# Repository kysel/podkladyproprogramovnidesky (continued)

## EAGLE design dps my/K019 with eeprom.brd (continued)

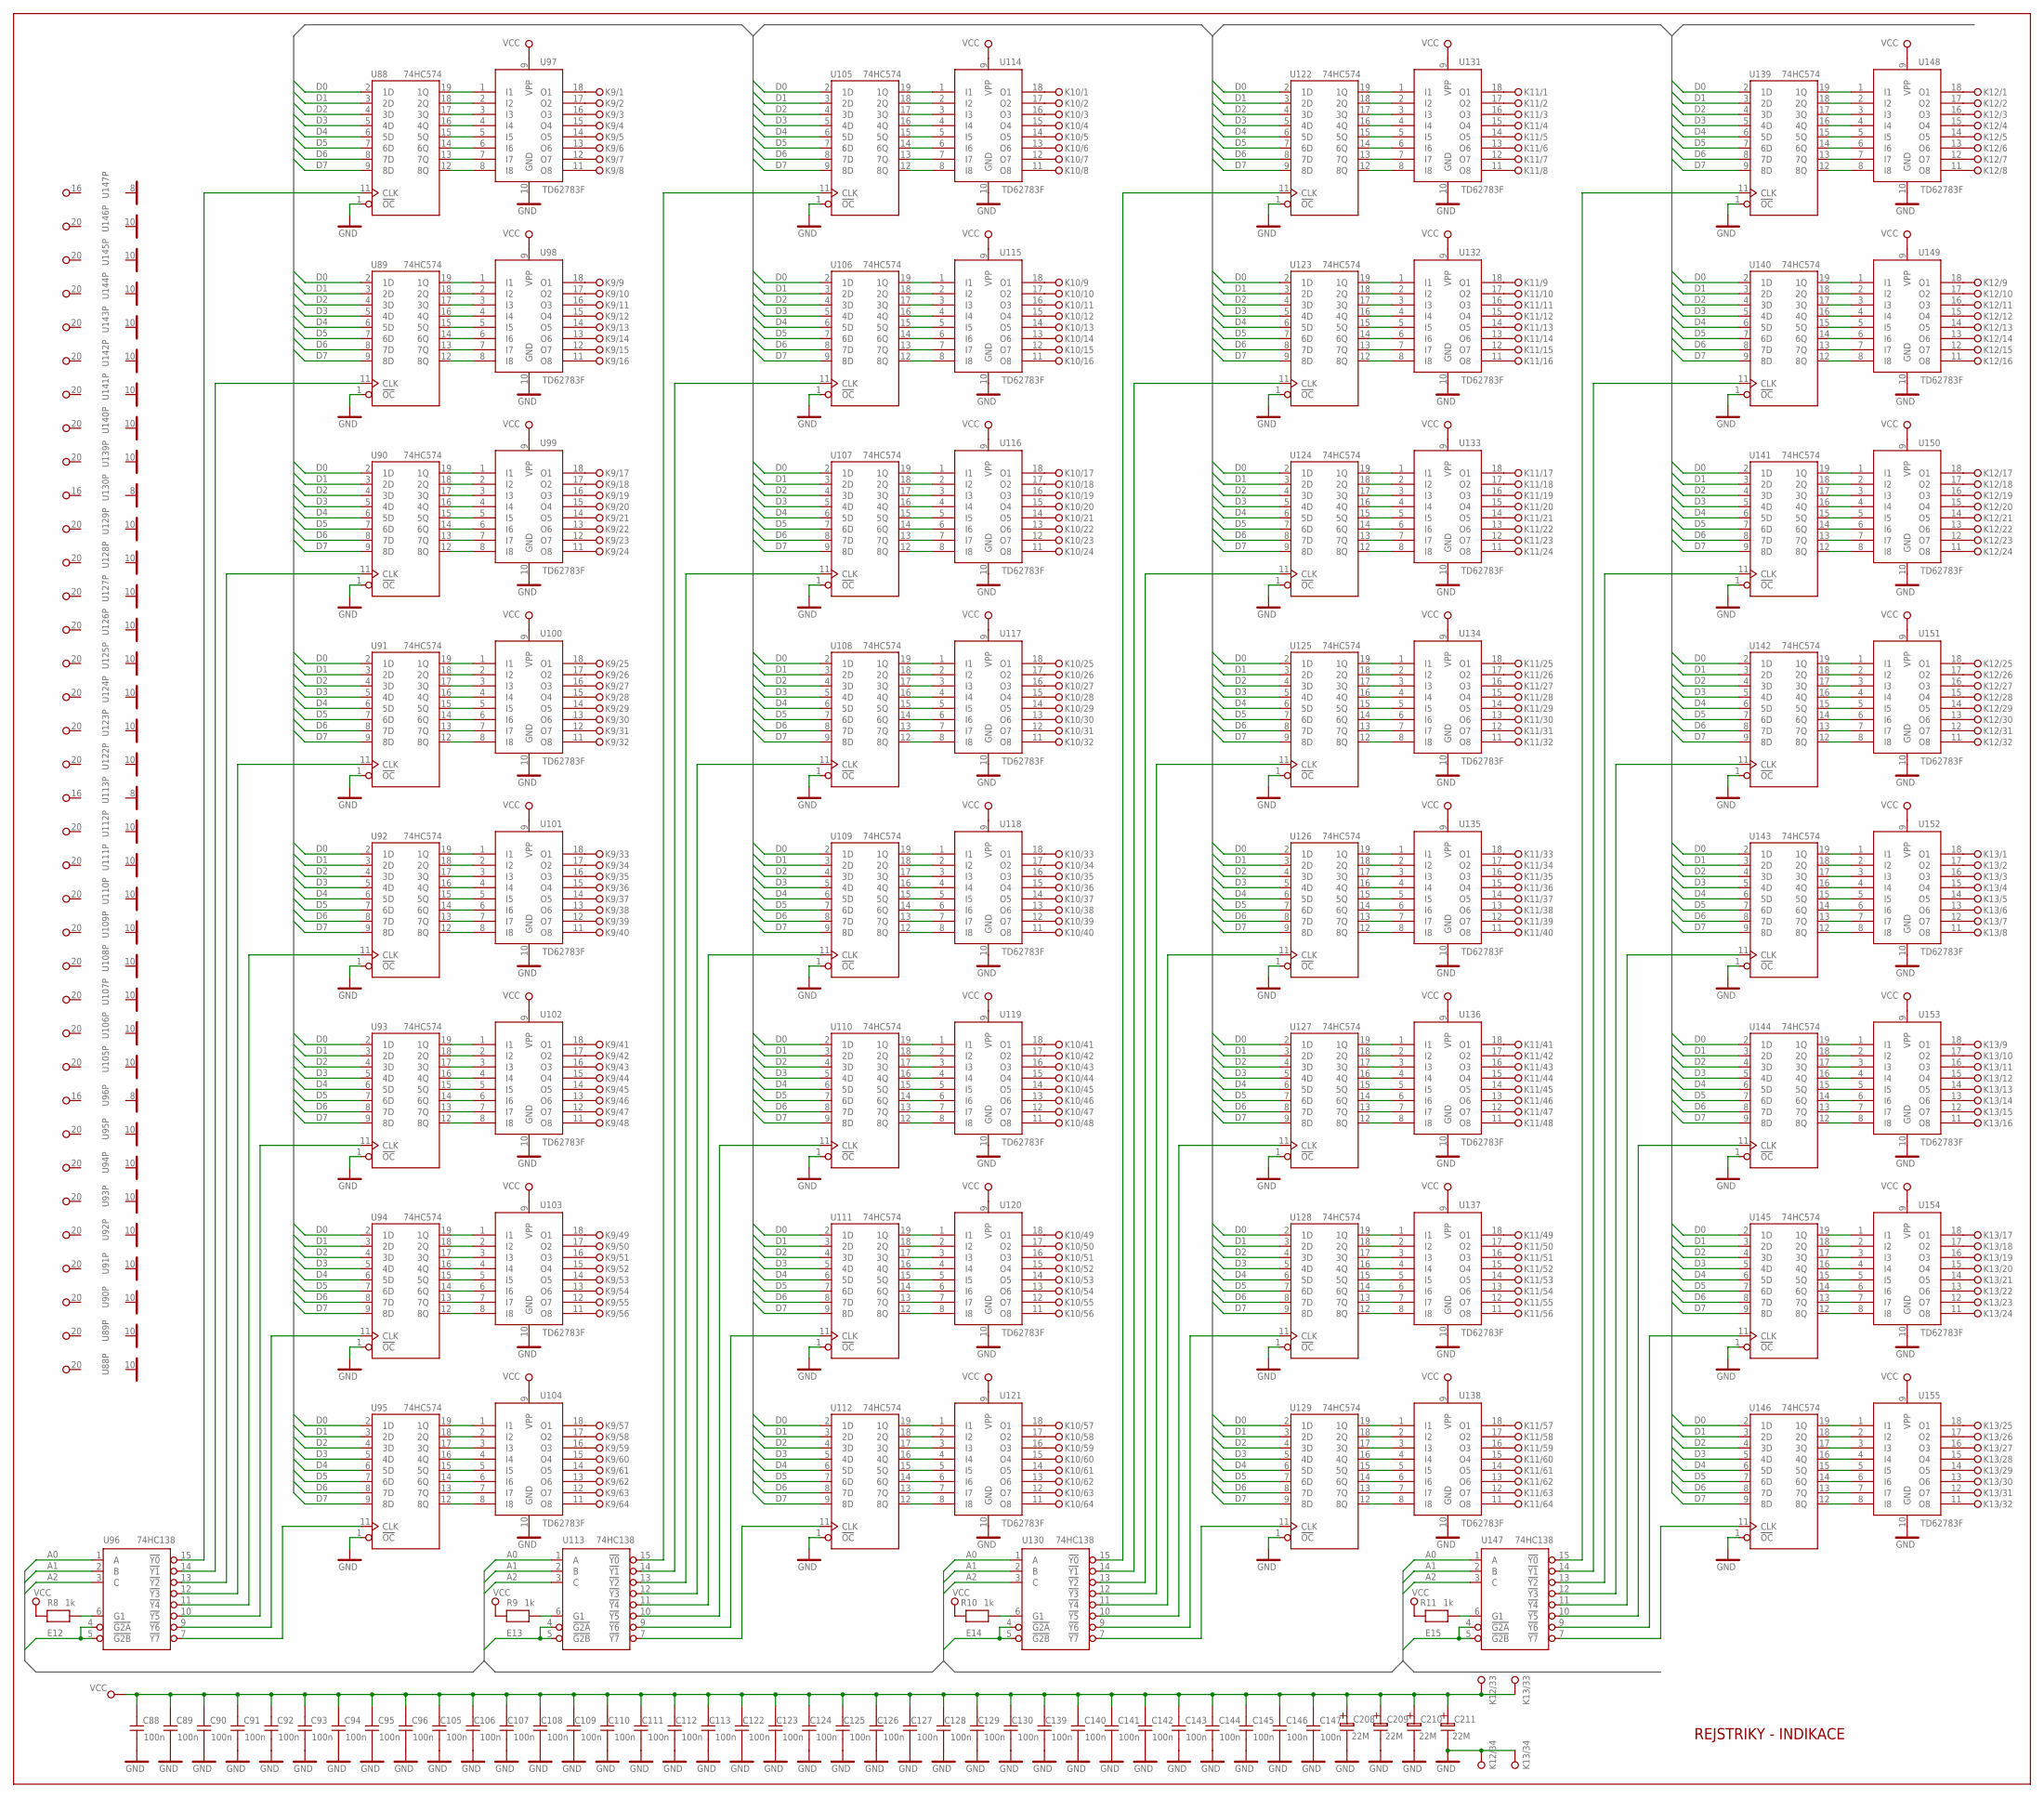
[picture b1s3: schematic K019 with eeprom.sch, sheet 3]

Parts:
C88, C89, C90, C91, C92, C93, C94, C95, C96, C105, C106, C107, C108, C109, C110, C111, C112, C113, C122, C123, C124, C125, C126, C127, C128, C129, C130, C139, C140, C141, C142, C143, C144, C145, C146, C147: 100n; C-5-2X8
C208, C209, C210, C211: 22M; EC-2/5
K9, K10, K11: KON64
K12, K13: KON34
R8, R9, R10, R11: 1k; R-7,5
U88, U89, U90, U91, U92, U93, U94, U95, U105, U106, U107, U108, U109, U110, U111, U112, U122, U123, U124, U125, U126, U127, U128, U129, U139, U140, U141, U142, U143, U144, U145, U146: 74HC574; DIL20
U96, U113, U130, U147: 74HC138; DIL16
U97, U98, U99, U100, U101, U102, U103, U104, U114, U115, U116, U117, U118, U119, U120, U121, U131, U132, U133, U134, U135, U136, U137, U138, U148, U149, U150, U151, U152, U153, U154, U155: TD62783F; DIL18

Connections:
A0: U96.1 (A), U113.1 (A), U130.1 (A), U147.1 (A); also elsewhere on the board
A1: U96.2 (B), U113.2 (B), U130.2 (B), U147.2 (B); also elsewhere on the board
A2: U96.3 (C), U113.3 (C), U130.3 (C), U147.3 (C); also elsewhere on the board
D0: U88.2 (1D), U89.2 (1D), U90.2 (1D), U91.2 (1D), U92.2 (1D), U93.2 (1D), U94.2 (1D), U95.2 (1D), U105.2 (1D), U106.2 (1D), U107.2 (1D), U108.2 (1D), U109.2 (1D), U110.2 (1D), U111.2 (1D), U112.2 (1D), U122.2 (1D), U123.2 (1D), U124.2 (1D), U125.2 (1D), U126.2 (1D), U127.2 (1D), U128.2 (1D), U129.2 (1D), U139.2 (1D), U140.2 (1D), U141.2 (1D), U142.2 (1D), U143.2 (1D), U144.2 (1D), U145.2 (1D), U146.2 (1D); also elsewhere on the board
D1: U88.3 (2D), U89.3 (2D), U90.3 (2D), U91.3 (2D), U92.3 (2D), U93.3 (2D), U94.3 (2D), U95.3 (2D), U105.3 (2D), U106.3 (2D), U107.3 (2D), U108.3 (2D), U109.3 (2D), U110.3 (2D), U111.3 (2D), U112.3 (2D), U122.3 (2D), U123.3 (2D), U124.3 (2D), U125.3 (2D), U126.3 (2D), U127.3 (2D), U128.3 (2D), U129.3 (2D), U139.3 (2D), U140.3 (2D), U141.3 (2D), U142.3 (2D), U143.3 (2D), U144.3 (2D), U145.3 (2D), U146.3 (2D); also elsewhere on the board
D2: U88.4 (3D), U89.4 (3D), U90.4 (3D), U91.4 (3D), U92.4 (3D), U93.4 (3D), U94.4 (3D), U95.4 (3D), U105.4 (3D), U106.4 (3D), U107.4 (3D), U108.4 (3D), U109.4 (3D), U110.4 (3D), U111.4 (3D), U112.4 (3D), U122.4 (3D), U123.4 (3D), U124.4 (3D), U125.4 (3D), U126.4 (3D), U127.4 (3D), U128.4 (3D), U129.4 (3D), U139.4 (3D), U140.4 (3D), U141.4 (3D), U142.4 (3D), U143.4 (3D), U144.4 (3D), U145.4 (3D), U146.4 (3D); also elsewhere on the board
D3: U88.5 (4D), U89.5 (4D), U90.5 (4D), U91.5 (4D), U92.5 (4D), U93.5 (4D), U94.5 (4D), U95.5 (4D), U105.5 (4D), U106.5 (4D), U107.5 (4D), U108.5 (4D), U109.5 (4D), U110.5 (4D), U111.5 (4D), U112.5 (4D), U122.5 (4D), U123.5 (4D), U124.5 (4D), U125.5 (4D), U126.5 (4D), U127.5 (4D), U128.5 (4D), U129.5 (4D), U139.5 (4D), U140.5 (4D), U141.5 (4D), U142.5 (4D), U143.5 (4D), U144.5 (4D), U145.5 (4D), U146.5 (4D); also elsewhere on the board
D4: U88.6 (5D), U89.6 (5D), U90.6 (5D), U91.6 (5D), U92.6 (5D), U93.6 (5D), U94.6 (5D), U95.6 (5D), U105.6 (5D), U106.6 (5D), U107.6 (5D), U108.6 (5D), U109.6 (5D), U110.6 (5D), U111.6 (5D), U112.6 (5D), U122.6 (5D), U123.6 (5D), U124.6 (5D), U125.6 (5D), U126.6 (5D), U127.6 (5D), U128.6 (5D), U129.6 (5D), U139.6 (5D), U140.6 (5D), U141.6 (5D), U142.6 (5D), U143.6 (5D), U144.6 (5D), U145.6 (5D), U146.6 (5D); also elsewhere on the board
D5: U88.7 (6D), U89.7 (6D), U90.7 (6D), U91.7 (6D), U92.7 (6D), U93.7 (6D), U94.7 (6D), U95.7 (6D), U105.7 (6D), U106.7 (6D), U107.7 (6D), U108.7 (6D), U109.7 (6D), U110.7 (6D), U111.7 (6D), U112.7 (6D), U122.7 (6D), U123.7 (6D), U124.7 (6D), U125.7 (6D), U126.7 (6D), U127.7 (6D), U128.7 (6D), U129.7 (6D), U139.7 (6D), U140.7 (6D), U141.7 (6D), U142.7 (6D), U143.7 (6D), U144.7 (6D), U145.7 (6D), U146.7 (6D); also elsewhere on the board
D6: U88.8 (7D), U89.8 (7D), U90.8 (7D), U91.8 (7D), U92.8 (7D), U93.8 (7D), U94.8 (7D), U95.8 (7D), U105.8 (7D), U106.8 (7D), U107.8 (7D), U108.8 (7D), U109.8 (7D), U110.8 (7D), U111.8 (7D), U112.8 (7D), U122.8 (7D), U123.8 (7D), U124.8 (7D), U125.8 (7D), U126.8 (7D), U127.8 (7D), U128.8 (7D), U129.8 (7D), U139.8 (7D), U140.8 (7D), U141.8 (7D), U142.8 (7D), U143.8 (7D), U144.8 (7D), U145.8 (7D), U146.8 (7D); also elsewhere on the board
D7: U88.9 (8D), U89.9 (8D), U90.9 (8D), U91.9 (8D), U92.9 (8D), U93.9 (8D), U94.9 (8D), U95.9 (8D), U105.9 (8D), U106.9 (8D), U107.9 (8D), U108.9 (8D), U109.9 (8D), U110.9 (8D), U111.9 (8D), U112.9 (8D), U122.9 (8D), U123.9 (8D), U124.9 (8D), U125.9 (8D), U126.9 (8D), U127.9 (8D), U128.9 (8D), U129.9 (8D), U139.9 (8D), U140.9 (8D), U141.9 (8D), U142.9 (8D), U143.9 (8D), U144.9 (8D), U145.9 (8D), U146.9 (8D); also elsewhere on the board
E12: U96.4 (!G2A), U96.5 (!G2B); also elsewhere on the board
E13: U113.4 (!G2A), U113.5 (!G2B); also elsewhere on the board
E14: U130.4 (!G2A), U130.5 (!G2B); also elsewhere on the board
E15: U147.4 (!G2A), U147.5 (!G2B); also elsewhere on the board
GND: C88.1, C89.1, C90.1, C91.1, C92.1, C93.1, C94.1, C95.1, C96.1, C105.1, C106.1, C107.1, C108.1, C109.1, C110.1, C111.1, C112.1, C113.1, C122.1, C123.1, C124.1, C125.1, C126.1, C127.1, C128.1, C129.1, C130.1, C139.1, C140.1, C141.1, C142.1, C143.1, C144.1, C145.1, C146.1, C147.1, C208.1, C209.1, C210.1, C211.1, K12.34, K13.34, U88.1 (!OC), U88.10 (GND), U89.1 (!OC), U89.10 (GND), U90.1 (!OC), U90.10 (GND), U91.1 (!OC), U91.10 (GND), U92.1 (!OC), U92.10 (GND), U93.1 (!OC), U93.10 (GND), U94.1 (!OC), U94.10 (GND), U95.1 (!OC), U95.10 (GND), U96.8 (GND), U97.10 (GND), U98.10 (GND), U99.10 (GND), U100.10 (GND), U101.10 (GND), U102.10 (GND), U103.10 (GND), U104.10 (GND), U105.1 (!OC), U105.10 (GND), U106.1 (!OC), U106.10 (GND), U107.1 (!OC), U107.10 (GND), U108.1 (!OC), U108.10 (GND), U109.1 (!OC), U109.10 (GND), U110.1 (!OC), U110.10 (GND), U111.1 (!OC), U111.10 (GND), U112.1 (!OC), U112.10 (GND), U113.8 (GND), U114.10 (GND), U115.10 (GND), U116.10 (GND), U117.10 (GND), U118.10 (GND), U119.10 (GND), U120.10 (GND), U121.10 (GND), U122.1 (!OC), U122.10 (GND), U123.1 (!OC), U123.10 (GND), U124.1 (!OC), U124.10 (GND), U125.1 (!OC), U125.10 (GND), U126.1 (!OC), U126.10 (GND), U127.1 (!OC), U127.10 (GND), U128.1 (!OC), U128.10 (GND), U129.1 (!OC), U129.10 (GND), U130.8 (GND), U131.10 (GND), U132.10 (GND), U133.10 (GND), U134.10 (GND), U135.10 (GND), U136.10 (GND), U137.10 (GND), U138.10 (GND), U139.1 (!OC), U139.10 (GND), U140.1 (!OC), U140.10 (GND), U141.1 (!OC), U141.10 (GND), U142.1 (!OC), U142.10 (GND), U143.1 (!OC), U143.10 (GND), U144.1 (!OC), U144.10 (GND), U145.1 (!OC), U145.10 (GND), U146.1 (!OC), U146.10 (GND), U147.8 (GND), U148.10 (GND), U149.10 (GND), U150.10 (GND), U151.10 (GND), U152.10 (GND), U153.10 (GND), U154.10 (GND), U155.10 (GND); also elsewhere on the board
unnamed: U88.19 (1Q), U97.1 (I1)
unnamed: U88.18 (2Q), U97.2 (I2)
unnamed: U88.17 (3Q), U97.3 (I3)
unnamed: U88.16 (4Q), U97.4 (I4)
unnamed: U88.15 (5Q), U97.5 (I5)
unnamed: U88.14 (6Q), U97.6 (I6)
unnamed: U88.13 (7Q), U97.7 (I7)
unnamed: U88.12 (8Q), U97.8 (I8)
unnamed: U89.19 (1Q), U98.1 (I1)
unnamed: K9.1, U97.18 (O1)
unnamed: K9.2, U97.17 (O2)
unnamed: U89.18 (2Q), U98.2 (I2)
unnamed: U89.17 (3Q), U98.3 (I3)
unnamed: U89.16 (4Q), U98.4 (I4)
unnamed: U89.15 (5Q), U98.5 (I5)
unnamed: U89.14 (6Q), U98.6 (I6)
unnamed: U89.13 (7Q), U98.7 (I7)
unnamed: U89.12 (8Q), U98.8 (I8)
unnamed: K9.3, U97.16 (O3)
unnamed: U90.19 (1Q), U99.1 (I1)
unnamed: U90.18 (2Q), U99.2 (I2)
unnamed: U90.17 (3Q), U99.3 (I3)
unnamed: U90.16 (4Q), U99.4 (I4)
unnamed: U90.15 (5Q), U99.5 (I5)
unnamed: U90.14 (6Q), U99.6 (I6)
unnamed: U90.13 (7Q), U99.7 (I7)
unnamed: U90.12 (8Q), U99.8 (I8)
unnamed: K9.4, U97.15 (O4)
unnamed: U91.19 (1Q), U100.1 (I1)
unnamed: U91.18 (2Q), U100.2 (I2)
unnamed: U91.17 (3Q), U100.3 (I3)
unnamed: U91.16 (4Q), U100.4 (I4)
unnamed: U91.15 (5Q), U100.5 (I5)
unnamed: U91.12 (8Q), U100.8 (I8)
unnamed: U91.13 (7Q), U100.7 (I7)
unnamed: U91.14 (6Q), U100.6 (I6)
unnamed: K9.5, U97.14 (O5)
unnamed: U92.19 (1Q), U101.1 (I1)
unnamed: U92.18 (2Q), U101.2 (I2)
unnamed: U92.17 (3Q), U101.3 (I3)
unnamed: U92.16 (4Q), U101.4 (I4)
unnamed: U92.15 (5Q), U101.5 (I5)
unnamed: U92.14 (6Q), U101.6 (I6)
unnamed: U92.13 (7Q), U101.7 (I7)
unnamed: U92.12 (8Q), U101.8 (I8)
unnamed: K9.6, U97.13 (O6)
unnamed: U93.19 (1Q), U102.1 (I1)
unnamed: U93.18 (2Q), U102.2 (I2)
unnamed: U93.17 (3Q), U102.3 (I3)
unnamed: U93.16 (4Q), U102.4 (I4)
unnamed: U93.15 (5Q), U102.5 (I5)
unnamed: U93.14 (6Q), U102.6 (I6)
unnamed: U93.13 (7Q), U102.7 (I7)
unnamed: U93.12 (8Q), U102.8 (I8)
unnamed: U94.19 (1Q), U103.1 (I1)
unnamed: U94.18 (2Q), U103.2 (I2)
unnamed: U94.17 (3Q), U103.3 (I3)
unnamed: U94.16 (4Q), U103.4 (I4)
unnamed: U94.15 (5Q), U103.5 (I5)
unnamed: U94.14 (6Q), U103.6 (I6)
unnamed: U94.13 (7Q), U103.7 (I7)
unnamed: U94.12 (8Q), U103.8 (I8)
unnamed: U95.19 (1Q), U104.1 (I1)
unnamed: U95.18 (2Q), U104.2 (I2)
unnamed: K9.7, U97.12 (O7)
unnamed: K9.8, U97.11 (O8)
unnamed: U95.17 (3Q), U104.3 (I3)
unnamed: U95.16 (4Q), U104.4 (I4)
unnamed: U95.15 (5Q), U104.5 (I5)
unnamed: U95.14 (6Q), U104.6 (I6)
unnamed: U95.13 (7Q), U104.7 (I7)
unnamed: U95.12 (8Q), U104.8 (I8)
unnamed: K9.9, U98.18 (O1)
unnamed: K9.10, U98.17 (O2)
unnamed: K9.11, U98.16 (O3)
unnamed: K9.12, U98.15 (O4)
unnamed: K9.13, U98.14 (O5)
unnamed: K9.14, U98.13 (O6)
unnamed: K9.15, U98.12 (O7)
unnamed: K9.16, U98.11 (O8)
unnamed: K9.17, U99.18 (O1)
unnamed: K9.18, U99.17 (O2)
unnamed: K9.19, U99.16 (O3)
unnamed: K9.20, U99.15 (O4)
unnamed: K9.21, U99.14 (O5)
unnamed: K9.22, U99.13 (O6)
unnamed: K9.23, U99.12 (O7)
unnamed: K9.24, U99.11 (O8)
unnamed: K9.25, U100.18 (O1)
unnamed: K9.26, U100.17 (O2)
unnamed: K9.27, U100.16 (O3)
unnamed: K9.28, U100.15 (O4)
unnamed: K9.29, U100.14 (O5)
unnamed: K9.30, U100.13 (O6)
unnamed: K9.31, U100.12 (O7)
unnamed: K9.32, U100.11 (O8)
unnamed: K9.33, U101.18 (O1)
unnamed: K9.34, U101.17 (O2)
unnamed: K9.35, U101.16 (O3)
unnamed: K9.36, U101.15 (O4)
unnamed: K9.37, U101.14 (O5)
unnamed: K9.38, U101.13 (O6)
unnamed: K9.39, U101.12 (O7)
unnamed: K9.40, U101.11 (O8)
unnamed: K9.41, U102.18 (O1)
unnamed: K9.42, U102.17 (O2)
unnamed: K9.43, U102.16 (O3)
unnamed: K9.44, U102.15 (O4)
unnamed: K9.45, U102.14 (O5)
unnamed: K9.46, U102.13 (O6)
unnamed: K9.47, U102.12 (O7)
unnamed: K9.48, U102.11 (O8)
unnamed: K9.49, U103.18 (O1)
unnamed: K9.50, U103.17 (O2)
unnamed: K9.51, U103.16 (O3)
unnamed: K9.52, U103.15 (O4)
unnamed: K9.53, U103.14 (O5)
unnamed: K9.54, U103.13 (O6)
unnamed: K9.55, U103.12 (O7)
unnamed: K9.56, U103.11 (O8)
unnamed: K9.57, U104.18 (O1)
unnamed: K9.58, U104.17 (O2)
unnamed: K9.59, U104.16 (O3)
unnamed: K9.60, U104.15 (O4)
unnamed: K9.61, U104.14 (O5)
unnamed: K9.62, U104.13 (O6)
unnamed: K9.63, U104.12 (O7)
unnamed: K9.64, U104.11 (O8)
unnamed: U94.11 (CLK), U96.9 (!Y6)
unnamed: U93.11 (CLK), U96.10 (!Y5)
unnamed: U92.11 (CLK), U96.11 (!Y4)
unnamed: U91.11 (CLK), U96.12 (!Y3)
unnamed: U90.11 (CLK), U96.13 (!Y2)
unnamed: U89.11 (CLK), U96.14 (!Y1)
unnamed: U88.11 (CLK), U96.15 (!Y0)
unnamed: U95.11 (CLK), U96.7 (!Y7)
unnamed: R8.2, U96.6 (G1)
unnamed: U111.11 (CLK), U113.9 (!Y6)
unnamed: U110.11 (CLK), U113.10 (!Y5)
unnamed: U109.11 (CLK), U113.11 (!Y4)
unnamed: U108.11 (CLK), U113.12 (!Y3)
unnamed: U107.11 (CLK), U113.13 (!Y2)
unnamed: U106.11 (CLK), U113.14 (!Y1)
unnamed: U105.11 (CLK), U113.15 (!Y0)
unnamed: U112.11 (CLK), U113.7 (!Y7)
unnamed: R9.2, U113.6 (G1)
unnamed: U105.19 (1Q), U114.1 (I1)
unnamed: U105.18 (2Q), U114.2 (I2)
unnamed: U105.17 (3Q), U114.3 (I3)
unnamed: U105.16 (4Q), U114.4 (I4)
unnamed: U105.15 (5Q), U114.5 (I5)
unnamed: U105.14 (6Q), U114.6 (I6)
unnamed: U105.13 (7Q), U114.7 (I7)
unnamed: U105.12 (8Q), U114.8 (I8)
unnamed: U106.19 (1Q), U115.1 (I1)
unnamed: U106.18 (2Q), U115.2 (I2)
unnamed: U106.17 (3Q), U115.3 (I3)
unnamed: U106.16 (4Q), U115.4 (I4)
unnamed: U106.15 (5Q), U115.5 (I5)
unnamed: U106.14 (6Q), U115.6 (I6)
unnamed: U106.13 (7Q), U115.7 (I7)
unnamed: U106.12 (8Q), U115.8 (I8)
unnamed: U107.19 (1Q), U116.1 (I1)
unnamed: U107.18 (2Q), U116.2 (I2)
unnamed: U107.17 (3Q), U116.3 (I3)
unnamed: U107.16 (4Q), U116.4 (I4)
unnamed: U107.15 (5Q), U116.5 (I5)
unnamed: U107.14 (6Q), U116.6 (I6)
unnamed: U107.13 (7Q), U116.7 (I7)
unnamed: U107.12 (8Q), U116.8 (I8)
unnamed: U108.19 (1Q), U117.1 (I1)
unnamed: U108.18 (2Q), U117.2 (I2)
unnamed: U108.17 (3Q), U117.3 (I3)
unnamed: U108.16 (4Q), U117.4 (I4)
unnamed: U108.15 (5Q), U117.5 (I5)
unnamed: U108.14 (6Q), U117.6 (I6)
unnamed: U108.13 (7Q), U117.7 (I7)
unnamed: U108.12 (8Q), U117.8 (I8)
unnamed: U109.19 (1Q), U118.1 (I1)
unnamed: U109.18 (2Q), U118.2 (I2)
unnamed: U109.17 (3Q), U118.3 (I3)
unnamed: U109.16 (4Q), U118.4 (I4)
unnamed: U109.15 (5Q), U118.5 (I5)
unnamed: U109.14 (6Q), U118.6 (I6)
unnamed: U109.13 (7Q), U118.7 (I7)
unnamed: U109.12 (8Q), U118.8 (I8)
unnamed: U110.19 (1Q), U119.1 (I1)
unnamed: U110.18 (2Q), U119.2 (I2)
unnamed: U110.17 (3Q), U119.3 (I3)
unnamed: U110.16 (4Q), U119.4 (I4)
unnamed: U110.15 (5Q), U119.5 (I5)
unnamed: U110.14 (6Q), U119.6 (I6)
unnamed: U110.13 (7Q), U119.7 (I7)
unnamed: U110.12 (8Q), U119.8 (I8)
unnamed: U111.19 (1Q), U120.1 (I1)
unnamed: U111.18 (2Q), U120.2 (I2)
unnamed: U111.17 (3Q), U120.3 (I3)
unnamed: U111.16 (4Q), U120.4 (I4)
unnamed: U111.15 (5Q), U120.5 (I5)
unnamed: U111.14 (6Q), U120.6 (I6)
unnamed: U111.13 (7Q), U120.7 (I7)
unnamed: U111.12 (8Q), U120.8 (I8)
unnamed: U112.19 (1Q), U121.1 (I1)
unnamed: U112.18 (2Q), U121.2 (I2)
unnamed: U112.17 (3Q), U121.3 (I3)
unnamed: U112.16 (4Q), U121.4 (I4)
unnamed: U112.15 (5Q), U121.5 (I5)
unnamed: U112.14 (6Q), U121.6 (I6)
unnamed: U112.13 (7Q), U121.7 (I7)
unnamed: U112.12 (8Q), U121.8 (I8)
unnamed: K10.1, U114.18 (O1)
unnamed: K10.2, U114.17 (O2)
unnamed: K10.3, U114.16 (O3)
unnamed: K10.4, U114.15 (O4)
unnamed: K10.5, U114.14 (O5)
unnamed: K10.6, U114.13 (O6)
unnamed: K10.7, U114.12 (O7)
unnamed: K10.8, U114.11 (O8)
unnamed: K10.9, U115.18 (O1)
unnamed: K10.10, U115.17 (O2)
unnamed: K10.11, U115.16 (O3)
unnamed: K10.12, U115.15 (O4)
unnamed: K10.13, U115.14 (O5)
unnamed: K10.14, U115.13 (O6)
unnamed: K10.15, U115.12 (O7)
unnamed: K10.16, U115.11 (O8)
unnamed: K10.17, U116.18 (O1)
unnamed: K10.18, U116.17 (O2)
unnamed: K10.19, U116.16 (O3)
unnamed: K10.20, U116.15 (O4)
unnamed: K10.21, U116.14 (O5)
unnamed: K10.22, U116.13 (O6)
unnamed: K10.23, U116.12 (O7)
unnamed: K10.24, U116.11 (O8)
unnamed: K10.25, U117.18 (O1)
unnamed: K10.26, U117.17 (O2)
unnamed: K10.27, U117.16 (O3)
unnamed: K10.28, U117.15 (O4)
unnamed: K10.29, U117.14 (O5)
unnamed: K10.30, U117.13 (O6)
unnamed: K10.31, U117.12 (O7)
unnamed: K10.32, U117.11 (O8)
unnamed: K10.33, U118.18 (O1)
unnamed: K10.34, U118.17 (O2)
unnamed: K10.35, U118.16 (O3)
unnamed: K10.36, U118.15 (O4)
unnamed: K10.37, U118.14 (O5)
unnamed: K10.38, U118.13 (O6)
unnamed: K10.39, U118.12 (O7)
unnamed: K10.40, U118.11 (O8)
unnamed: K10.41, U119.18 (O1)
unnamed: K10.42, U119.17 (O2)
unnamed: K10.43, U119.16 (O3)
unnamed: K10.44, U119.15 (O4)
unnamed: K10.45, U119.14 (O5)
unnamed: K10.46, U119.13 (O6)
unnamed: K10.47, U119.12 (O7)
unnamed: K10.48, U119.11 (O8)
unnamed: K10.49, U120.18 (O1)
unnamed: K10.50, U120.17 (O2)
unnamed: K10.51, U120.16 (O3)
unnamed: K10.52, U120.15 (O4)
unnamed: K10.53, U120.14 (O5)
unnamed: K10.54, U120.13 (O6)
unnamed: K10.55, U120.12 (O7)
unnamed: K10.56, U120.11 (O8)
unnamed: K10.57, U121.18 (O1)
unnamed: K10.58, U121.17 (O2)
unnamed: K10.59, U121.16 (O3)
unnamed: K10.60, U121.15 (O4)
unnamed: K10.61, U121.14 (O5)
unnamed: K10.62, U121.13 (O6)
unnamed: K10.63, U121.12 (O7)
unnamed: K10.64, U121.11 (O8)
unnamed: U128.11 (CLK), U130.9 (!Y6)
unnamed: U127.11 (CLK), U130.10 (!Y5)
unnamed: U126.11 (CLK), U130.11 (!Y4)
unnamed: U125.11 (CLK), U130.12 (!Y3)
unnamed: U124.11 (CLK), U130.13 (!Y2)
unnamed: U123.11 (CLK), U130.14 (!Y1)
unnamed: U122.11 (CLK), U130.15 (!Y0)
unnamed: U129.11 (CLK), U130.7 (!Y7)
unnamed: R10.2, U130.6 (G1)
unnamed: U122.19 (1Q), U131.1 (I1)
unnamed: U122.18 (2Q), U131.2 (I2)
unnamed: U122.17 (3Q), U131.3 (I3)
unnamed: U122.16 (4Q), U131.4 (I4)
unnamed: U122.15 (5Q), U131.5 (I5)
unnamed: U122.14 (6Q), U131.6 (I6)
unnamed: U122.13 (7Q), U131.7 (I7)
unnamed: U122.12 (8Q), U131.8 (I8)
unnamed: U123.19 (1Q), U132.1 (I1)
unnamed: U123.18 (2Q), U132.2 (I2)
unnamed: U123.17 (3Q), U132.3 (I3)
unnamed: U123.16 (4Q), U132.4 (I4)
unnamed: U123.15 (5Q), U132.5 (I5)
unnamed: U123.14 (6Q), U132.6 (I6)
unnamed: U123.13 (7Q), U132.7 (I7)
unnamed: U123.12 (8Q), U132.8 (I8)
unnamed: U124.19 (1Q), U133.1 (I1)
unnamed: U124.18 (2Q), U133.2 (I2)
unnamed: U124.17 (3Q), U133.3 (I3)
unnamed: U124.16 (4Q), U133.4 (I4)
unnamed: U124.15 (5Q), U133.5 (I5)
unnamed: U124.14 (6Q), U133.6 (I6)
unnamed: U124.13 (7Q), U133.7 (I7)
unnamed: U124.12 (8Q), U133.8 (I8)
unnamed: U125.19 (1Q), U134.1 (I1)
unnamed: U125.18 (2Q), U134.2 (I2)
unnamed: U125.17 (3Q), U134.3 (I3)
unnamed: U125.16 (4Q), U134.4 (I4)
unnamed: U125.15 (5Q), U134.5 (I5)
unnamed: U125.14 (6Q), U134.6 (I6)
unnamed: U125.13 (7Q), U134.7 (I7)
unnamed: U125.12 (8Q), U134.8 (I8)
unnamed: U126.19 (1Q), U135.1 (I1)
unnamed: U126.18 (2Q), U135.2 (I2)
unnamed: U126.17 (3Q), U135.3 (I3)
unnamed: U126.16 (4Q), U135.4 (I4)
unnamed: U126.15 (5Q), U135.5 (I5)
unnamed: U126.14 (6Q), U135.6 (I6)
unnamed: U126.13 (7Q), U135.7 (I7)
unnamed: U126.12 (8Q), U135.8 (I8)
unnamed: U127.19 (1Q), U136.1 (I1)
unnamed: U127.18 (2Q), U136.2 (I2)
unnamed: U127.17 (3Q), U136.3 (I3)
unnamed: U127.16 (4Q), U136.4 (I4)
unnamed: U127.15 (5Q), U136.5 (I5)
unnamed: U127.14 (6Q), U136.6 (I6)
unnamed: U127.13 (7Q), U136.7 (I7)
unnamed: U127.12 (8Q), U136.8 (I8)
unnamed: U128.19 (1Q), U137.1 (I1)
unnamed: U128.18 (2Q), U137.2 (I2)
unnamed: U128.17 (3Q), U137.3 (I3)
unnamed: U128.16 (4Q), U137.4 (I4)
unnamed: U128.15 (5Q), U137.5 (I5)
unnamed: U128.14 (6Q), U137.6 (I6)
unnamed: U128.13 (7Q), U137.7 (I7)
unnamed: U128.12 (8Q), U137.8 (I8)
unnamed: U129.19 (1Q), U138.1 (I1)
unnamed: U129.18 (2Q), U138.2 (I2)
unnamed: U129.17 (3Q), U138.3 (I3)
unnamed: U129.16 (4Q), U138.4 (I4)
unnamed: U129.15 (5Q), U138.5 (I5)
unnamed: U129.14 (6Q), U138.6 (I6)
unnamed: U129.13 (7Q), U138.7 (I7)
unnamed: U129.12 (8Q), U138.8 (I8)
unnamed: K11.1, U131.18 (O1)
unnamed: K11.2, U131.17 (O2)
unnamed: K11.3, U131.16 (O3)
unnamed: K11.4, U131.15 (O4)
unnamed: K11.5, U131.14 (O5)
unnamed: K11.6, U131.13 (O6)
unnamed: K11.7, U131.12 (O7)
unnamed: K11.8, U131.11 (O8)
unnamed: K11.9, U132.18 (O1)
unnamed: K11.10, U132.17 (O2)
unnamed: K11.11, U132.16 (O3)
unnamed: K11.12, U132.15 (O4)
unnamed: K11.13, U132.14 (O5)
unnamed: K11.14, U132.13 (O6)
unnamed: K11.15, U132.12 (O7)
unnamed: K11.16, U132.11 (O8)
unnamed: K11.17, U133.18 (O1)
unnamed: K11.18, U133.17 (O2)
unnamed: K11.19, U133.16 (O3)
unnamed: K11.20, U133.15 (O4)
unnamed: K11.21, U133.14 (O5)
unnamed: K11.22, U133.13 (O6)
unnamed: K11.23, U133.12 (O7)
unnamed: K11.24, U133.11 (O8)
unnamed: K11.25, U134.18 (O1)
unnamed: K11.26, U134.17 (O2)
unnamed: K11.27, U134.16 (O3)
unnamed: K11.28, U134.15 (O4)
unnamed: K11.29, U134.14 (O5)
unnamed: K11.30, U134.13 (O6)
unnamed: K11.31, U134.12 (O7)
unnamed: K11.32, U134.11 (O8)
unnamed: K11.33, U135.18 (O1)
unnamed: K11.34, U135.17 (O2)
unnamed: K11.35, U135.16 (O3)
unnamed: K11.36, U135.15 (O4)
unnamed: K11.37, U135.14 (O5)
unnamed: K11.38, U135.13 (O6)
unnamed: K11.39, U135.12 (O7)
unnamed: K11.40, U135.11 (O8)
unnamed: K11.41, U136.18 (O1)
unnamed: K11.42, U136.17 (O2)
unnamed: K11.43, U136.16 (O3)
unnamed: K11.44, U136.15 (O4)
unnamed: K11.45, U136.14 (O5)
unnamed: K11.46, U136.13 (O6)
unnamed: K11.47, U136.12 (O7)
unnamed: K11.48, U136.11 (O8)
unnamed: K11.49, U137.18 (O1)
unnamed: K11.50, U137.17 (O2)
unnamed: K11.51, U137.16 (O3)
unnamed: K11.52, U137.15 (O4)
unnamed: K11.53, U137.14 (O5)
unnamed: K11.54, U137.13 (O6)
unnamed: K11.55, U137.12 (O7)
unnamed: K11.56, U137.11 (O8)
unnamed: K11.57, U138.18 (O1)
unnamed: K11.58, U138.17 (O2)
unnamed: K11.59, U138.16 (O3)
unnamed: K11.60, U138.15 (O4)
unnamed: K11.61, U138.14 (O5)
unnamed: K11.62, U138.13 (O6)
unnamed: K11.63, U138.12 (O7)
unnamed: K11.64, U138.11 (O8)
unnamed: U145.11 (CLK), U147.9 (!Y6)
unnamed: U144.11 (CLK), U147.10 (!Y5)
unnamed: U143.11 (CLK), U147.11 (!Y4)
unnamed: U142.11 (CLK), U147.12 (!Y3)
unnamed: U141.11 (CLK), U147.13 (!Y2)
unnamed: U140.11 (CLK), U147.14 (!Y1)
unnamed: U139.11 (CLK), U147.15 (!Y0)
unnamed: U146.11 (CLK), U147.7 (!Y7)
unnamed: R11.2, U147.6 (G1)
unnamed: U139.19 (1Q), U148.1 (I1)
unnamed: U139.18 (2Q), U148.2 (I2)
unnamed: U139.17 (3Q), U148.3 (I3)
unnamed: U139.16 (4Q), U148.4 (I4)
unnamed: U139.15 (5Q), U148.5 (I5)
unnamed: U139.14 (6Q), U148.6 (I6)
unnamed: U139.13 (7Q), U148.7 (I7)
unnamed: U139.12 (8Q), U148.8 (I8)
unnamed: U140.19 (1Q), U149.1 (I1)
unnamed: U140.18 (2Q), U149.2 (I2)
unnamed: U140.17 (3Q), U149.3 (I3)
unnamed: U140.16 (4Q), U149.4 (I4)
unnamed: U140.15 (5Q), U149.5 (I5)
unnamed: U140.14 (6Q), U149.6 (I6)
unnamed: U140.13 (7Q), U149.7 (I7)
unnamed: U140.12 (8Q), U149.8 (I8)
unnamed: U141.19 (1Q), U150.1 (I1)
unnamed: U141.18 (2Q), U150.2 (I2)
unnamed: U141.17 (3Q), U150.3 (I3)
unnamed: U141.16 (4Q), U150.4 (I4)
unnamed: U141.15 (5Q), U150.5 (I5)
unnamed: U141.14 (6Q), U150.6 (I6)
unnamed: U141.13 (7Q), U150.7 (I7)
unnamed: U141.12 (8Q), U150.8 (I8)
unnamed: U142.19 (1Q), U151.1 (I1)
unnamed: U142.18 (2Q), U151.2 (I2)
unnamed: U142.17 (3Q), U151.3 (I3)
unnamed: U142.16 (4Q), U151.4 (I4)
unnamed: U142.15 (5Q), U151.5 (I5)
unnamed: U142.14 (6Q), U151.6 (I6)
unnamed: U142.13 (7Q), U151.7 (I7)
unnamed: U142.12 (8Q), U151.8 (I8)
unnamed: U143.19 (1Q), U152.1 (I1)
unnamed: U143.18 (2Q), U152.2 (I2)
unnamed: U143.17 (3Q), U152.3 (I3)
unnamed: U143.16 (4Q), U152.4 (I4)
unnamed: U143.15 (5Q), U152.5 (I5)
unnamed: U143.14 (6Q), U152.6 (I6)
unnamed: U143.13 (7Q), U152.7 (I7)
unnamed: U143.12 (8Q), U152.8 (I8)
unnamed: U144.19 (1Q), U153.1 (I1)
unnamed: U144.18 (2Q), U153.2 (I2)
unnamed: U144.17 (3Q), U153.3 (I3)
unnamed: U144.16 (4Q), U153.4 (I4)
unnamed: U144.15 (5Q), U153.5 (I5)
unnamed: U144.14 (6Q), U153.6 (I6)
unnamed: U144.13 (7Q), U153.7 (I7)
unnamed: U144.12 (8Q), U153.8 (I8)
unnamed: U145.19 (1Q), U154.1 (I1)
unnamed: U145.18 (2Q), U154.2 (I2)
unnamed: U145.17 (3Q), U154.3 (I3)
unnamed: U145.16 (4Q), U154.4 (I4)
unnamed: U145.15 (5Q), U154.5 (I5)
unnamed: U145.14 (6Q), U154.6 (I6)
unnamed: U145.13 (7Q), U154.7 (I7)
unnamed: U145.12 (8Q), U154.8 (I8)
unnamed: U146.19 (1Q), U155.1 (I1)
unnamed: U146.18 (2Q), U155.2 (I2)
unnamed: U146.17 (3Q), U155.3 (I3)
unnamed: U146.16 (4Q), U155.4 (I4)
unnamed: U146.15 (5Q), U155.5 (I5)
unnamed: U146.14 (6Q), U155.6 (I6)
unnamed: U146.13 (7Q), U155.7 (I7)
unnamed: U146.12 (8Q), U155.8 (I8)
unnamed: K12.1, U148.18 (O1)
unnamed: K12.2, U148.17 (O2)
unnamed: K12.3, U148.16 (O3)
unnamed: K12.4, U148.15 (O4)
unnamed: K12.5, U148.14 (O5)
unnamed: K12.6, U148.13 (O6)
unnamed: K12.7, U148.12 (O7)
unnamed: K12.8, U148.11 (O8)
unnamed: K12.9, U149.18 (O1)
unnamed: K12.10, U149.17 (O2)
unnamed: K12.11, U149.16 (O3)
unnamed: K12.12, U149.15 (O4)
unnamed: K12.13, U149.14 (O5)
unnamed: K12.14, U149.13 (O6)
unnamed: K12.15, U149.12 (O7)
unnamed: K12.16, U149.11 (O8)
unnamed: K12.17, U150.18 (O1)
unnamed: K12.18, U150.17 (O2)
unnamed: K12.19, U150.16 (O3)
unnamed: K12.20, U150.15 (O4)
unnamed: K12.21, U150.14 (O5)
unnamed: K12.22, U150.13 (O6)
unnamed: K12.23, U150.12 (O7)
unnamed: K12.24, U150.11 (O8)
unnamed: K12.25, U151.18 (O1)
unnamed: K12.26, U151.17 (O2)
unnamed: K12.27, U151.16 (O3)
unnamed: K12.28, U151.15 (O4)
unnamed: K12.29, U151.14 (O5)
unnamed: K12.30, U151.13 (O6)
unnamed: K12.31, U151.12 (O7)
unnamed: K12.32, U151.11 (O8)
unnamed: K13.1, U152.18 (O1)
unnamed: K13.2, U152.17 (O2)
unnamed: K13.3, U152.16 (O3)
unnamed: K13.4, U152.15 (O4)
unnamed: K13.5, U152.14 (O5)
unnamed: K13.6, U152.13 (O6)
unnamed: K13.7, U152.12 (O7)
unnamed: K13.8, U152.11 (O8)
unnamed: K13.9, U153.18 (O1)
unnamed: K13.10, U153.17 (O2)
unnamed: K13.11, U153.16 (O3)
unnamed: K13.12, U153.15 (O4)
unnamed: K13.13, U153.14 (O5)
unnamed: K13.14, U153.13 (O6)
unnamed: K13.15, U153.12 (O7)
unnamed: K13.16, U153.11 (O8)
unnamed: K13.17, U154.18 (O1)
unnamed: K13.18, U154.17 (O2)
unnamed: K13.19, U154.16 (O3)
unnamed: K13.20, U154.15 (O4)
unnamed: K13.21, U154.14 (O5)
unnamed: K13.22, U154.13 (O6)
unnamed: K13.23, U154.12 (O7)
unnamed: K13.24, U154.11 (O8)
unnamed: K13.25, U155.18 (O1)
unnamed: K13.26, U155.17 (O2)
unnamed: K13.27, U155.16 (O3)
unnamed: K13.28, U155.15 (O4)
unnamed: K13.29, U155.14 (O5)
unnamed: K13.30, U155.13 (O6)
unnamed: K13.31, U155.12 (O7)
unnamed: K13.32, U155.11 (O8)
VCC: C88.2, C89.2, C90.2, C91.2, C92.2, C93.2, C94.2, C95.2, C96.2, C105.2, C106.2, C107.2, C108.2, C109.2, C110.2, C111.2, C112.2, C113.2, C122.2, C123.2, C124.2, C125.2, C126.2, C127.2, C128.2, C129.2, C130.2, C139.2, C140.2, C141.2, C142.2, C143.2, C144.2, C145.2, C146.2, C147.2, C208.2, C209.2, C210.2, C211.2, K12.33, K13.33, R8.1, R9.1, R10.1, R11.1, U88.20 (VCC), U89.20 (VCC), U90.20 (VCC), U91.20 (VCC), U92.20 (VCC), U93.20 (VCC), U94.20 (VCC), U95.20 (VCC), U96.16 (VCC), U97.9 (VPP), U98.9 (VPP), U99.9 (VPP), U100.9 (VPP), U101.9 (VPP), U102.9 (VPP), U103.9 (VPP), U104.9 (VPP), U105.20 (VCC), U106.20 (VCC), U107.20 (VCC), U108.20 (VCC), U109.20 (VCC), U110.20 (VCC), U111.20 (VCC), U112.20 (VCC), U113.16 (VCC), U114.9 (VPP), U115.9 (VPP), U116.9 (VPP), U117.9 (VPP), U118.9 (VPP), U119.9 (VPP), U120.9 (VPP), U121.9 (VPP), U122.20 (VCC), U123.20 (VCC), U124.20 (VCC), U125.20 (VCC), U126.20 (VCC), U127.20 (VCC), U128.20 (VCC), U129.20 (VCC), U130.16 (VCC), U131.9 (VPP), U132.9 (VPP), U133.9 (VPP), U134.9 (VPP), U135.9 (VPP), U136.9 (VPP), U137.9 (VPP), U138.9 (VPP), U139.20 (VCC), U140.20 (VCC), U141.20 (VCC), U142.20 (VCC), U143.20 (VCC), U144.20 (VCC), U145.20 (VCC), U146.20 (VCC), U147.16 (VCC), U148.9 (VPP), U149.9 (VPP), U150.9 (VPP), U151.9 (VPP), U152.9 (VPP), U153.9 (VPP), U154.9 (VPP), U155.9 (VPP); also elsewhere on the board

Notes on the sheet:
REJSTRIKY - INDIKACE
